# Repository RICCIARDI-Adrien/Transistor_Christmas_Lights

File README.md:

# Transistor Christmas Lights

A really simple blinking Christmas lights using only bipolar transistors for its logic.

## Circuits

The board is made of 2 separate circuits : the motherboard and the light.  
The motherboard circuit holds the logic while the light circuit contains the leds.  
The light circuit should be manufactured in about 20 copies.

## Circuit simulation

The circuit concept is simulated with [Logisim Evolution](https://github.com/logisim-evolution/logisim-evolution) version 3.7.2, the Logisim file is located [here](Motherboard/Simulation/Logisim_Simulation.circ).  
I tried to keep the gates count as low as possible and I tried to select gates that also minimize the transistors count.  
The Logicim file gathers some different tests for the same logic block, all these tests are still present in the file if needed.

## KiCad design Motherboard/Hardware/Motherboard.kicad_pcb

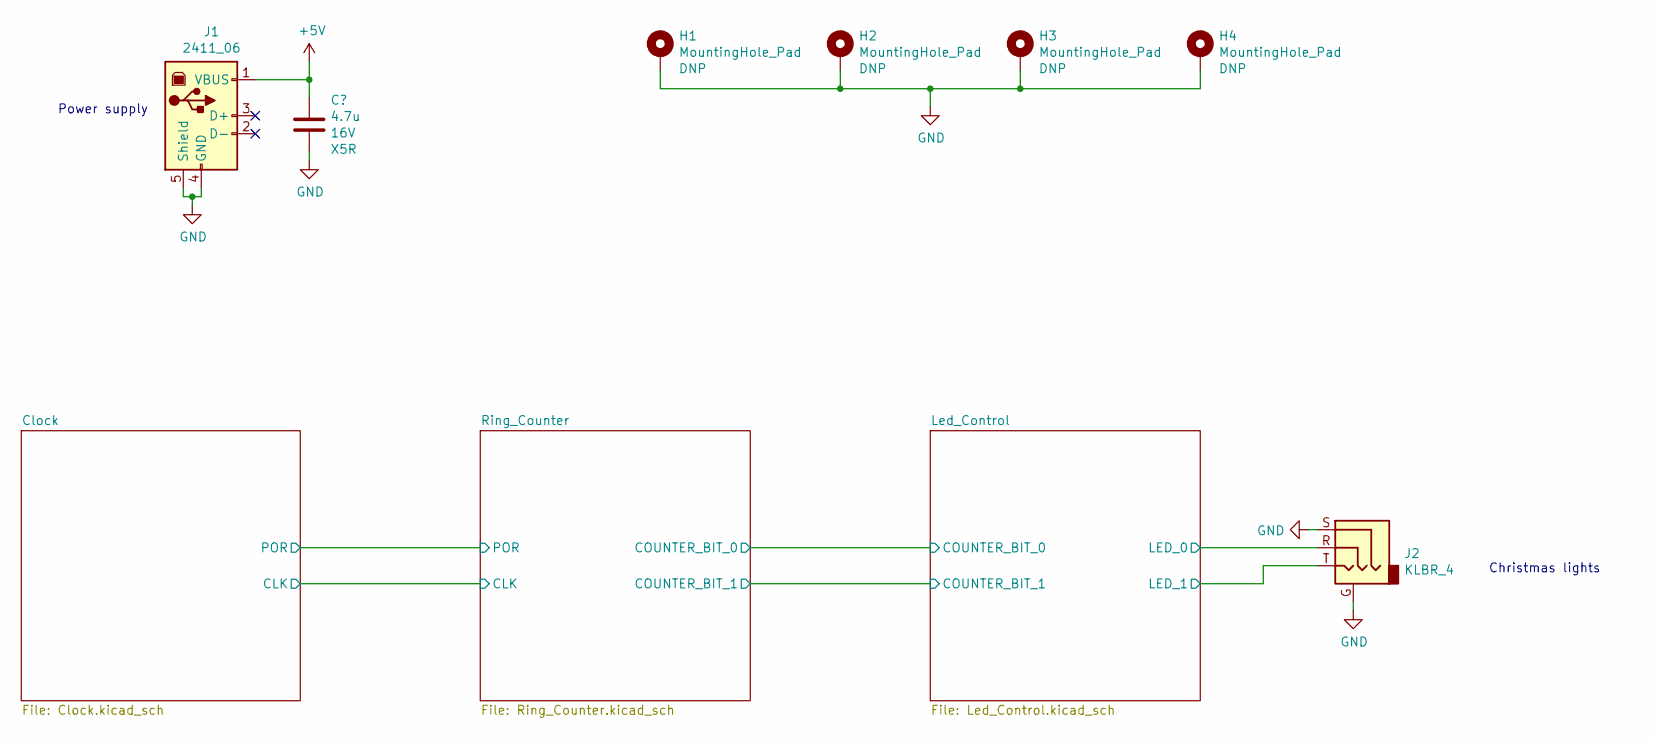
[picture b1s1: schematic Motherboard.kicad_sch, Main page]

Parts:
C1: 4.7u; C_0805_2012Metric_Pad1.18x1.45mm_HandSolder; PartNumber CL21A475KOFNNNE
H1, H2, H3, H4: MountingHole_Pad; MountingHole_4.5mm_Pad
J1: 2411_06; USB_B_OST_USB-B1HSxx_Horizontal; PartNumber 2411_06
J2: KLBR_4; PartNumber KLBR_4

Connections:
/Led_Control/LED_0: J2.R; also elsewhere on the board
/Led_Control/LED_1: J2.T; also elsewhere on the board
GND: C1.2, H1.1, H2.1, H3.1, H4.1, J1.4 (GND), J1.5 (Shield), J2.G, J2.S; also elsewhere on the board

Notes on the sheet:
Power supply
Christmas lights

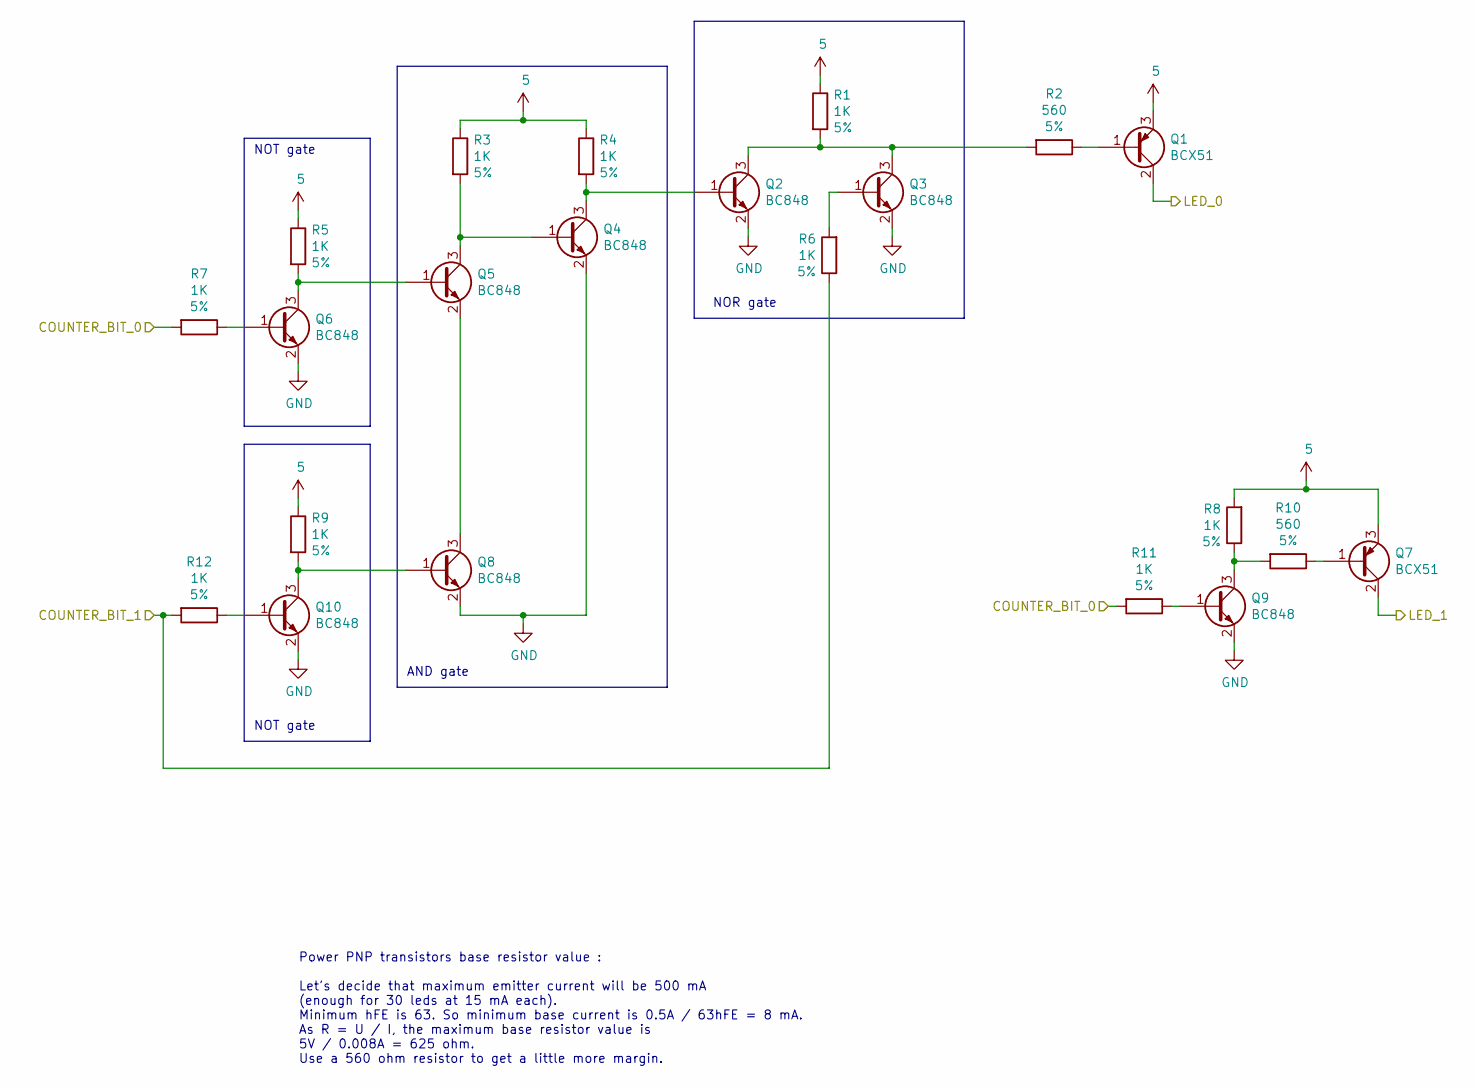
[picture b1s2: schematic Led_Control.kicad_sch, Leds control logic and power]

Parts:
Q1, Q7: BCX51; SOT-89-3; PartNumber BCX51,115
Q2, Q3, Q4, Q5, Q6, Q8, Q9, Q10: BC848; SOT-23
R1, R3, R4, R5, R6, R7, R8, R9, R11, R12: 1K; R_0603_1608Metric_Pad0.98x0.95mm_HandSolder
R2, R10: 560; R_0603_1608Metric_Pad0.98x0.95mm_HandSolder

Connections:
/Led_Control/COUNTER_BIT_0: R7.2, R11.2; also elsewhere on the board
/Led_Control/COUNTER_BIT_1: R6.1, R12.2; also elsewhere on the board
/Led_Control/LED_0: Q1.2 (C); also elsewhere on the board
/Led_Control/LED_1: Q7.2 (C); also elsewhere on the board
GND: Q2.2 (E), Q3.2 (E), Q4.2 (E), Q6.2 (E), Q8.2 (E), Q9.2 (E), Q10.2 (E); also elsewhere on the board
unnamed: Q1.1 (B), R2.1
unnamed: Q2.1 (B), Q4.3 (C), R4.2
unnamed: Q2.3 (C), Q3.3 (C), R1.2, R2.2
unnamed: Q3.1 (B), R6.2
unnamed: Q4.1 (B), Q5.3 (C), R3.2
unnamed: Q5.1 (B), Q6.3 (C), R5.2
unnamed: Q5.2 (E), Q8.3 (C)
unnamed: Q6.1 (B), R7.1
unnamed: Q7.1 (B), R10.1
unnamed: Q9.1 (B), R11.1
unnamed: Q9.3 (C), R8.1, R10.2
unnamed: Q10.1 (B), R12.1
unnamed: Q8.1 (B), Q10.3 (C), R9.2

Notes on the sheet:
NOT gate
Power PNP transistors base resistor value : Let's decide that maximum emitter current will be 500 mA (enough for 30 leds at 15 mA each). Minimum hFE is 63. So minimum base current is 0.5A / 63hFE = 8 mA. As R = U / I, the maximum base resistor value is 5V / 0.008A = 625 ohm. Use a 560 ohm resistor 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
NOR gate
AND gate

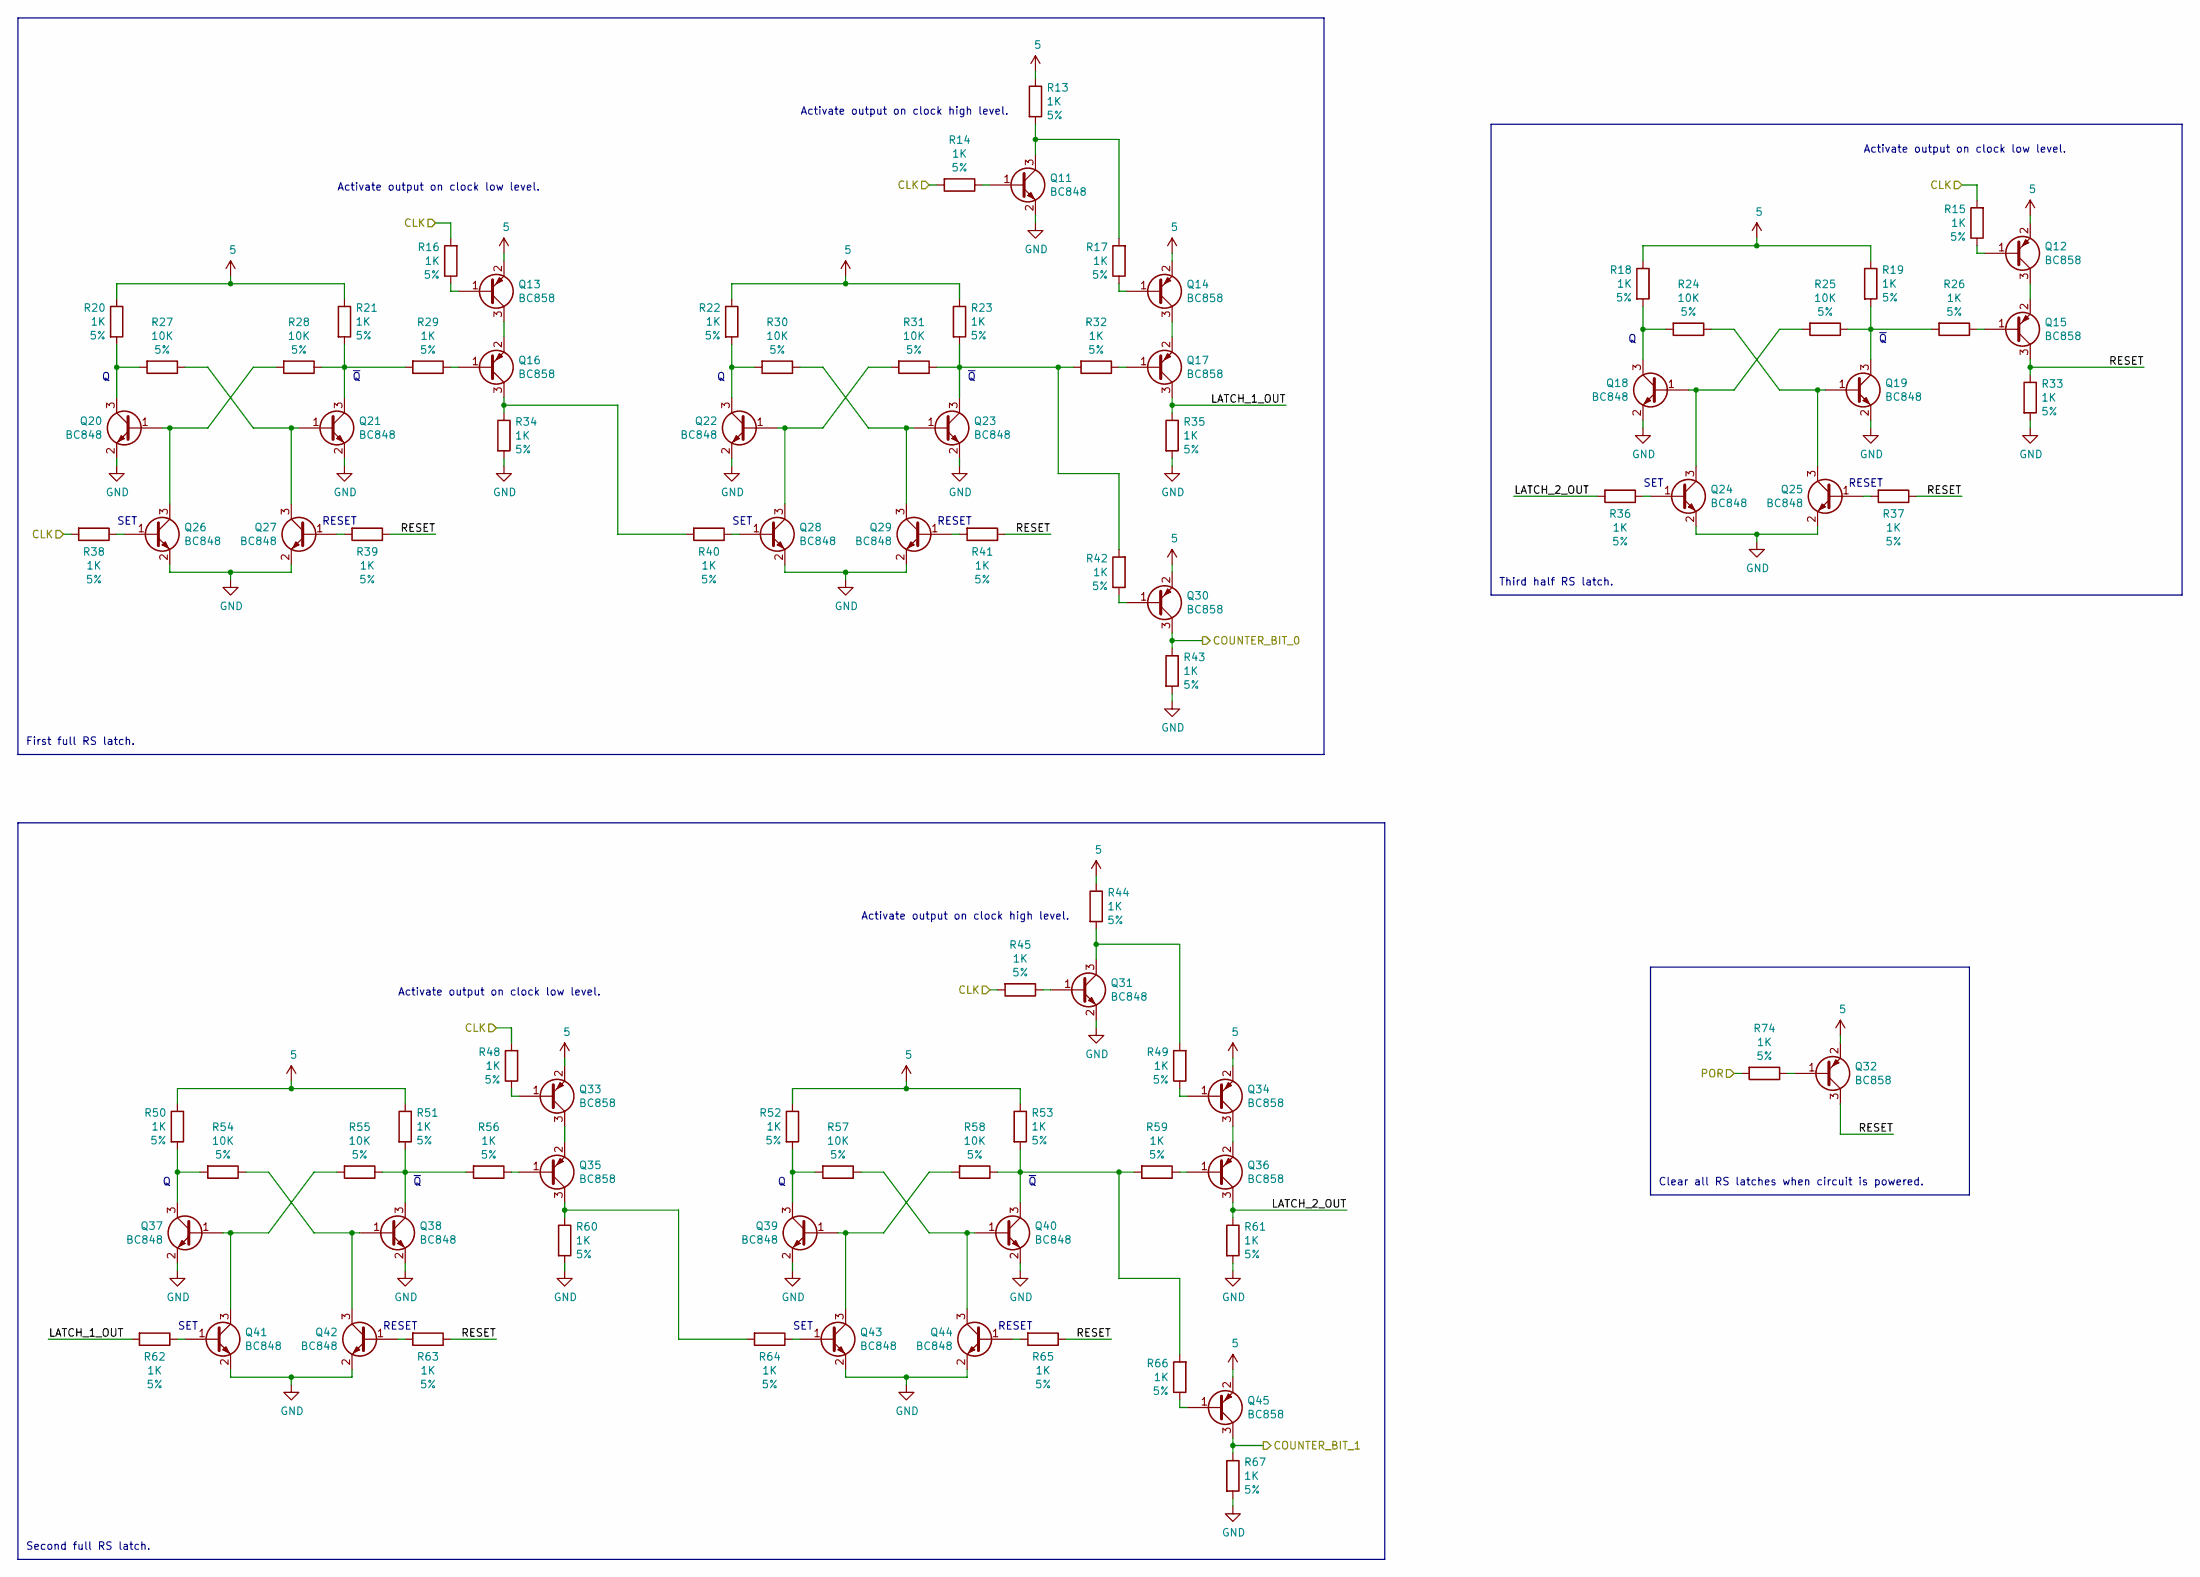
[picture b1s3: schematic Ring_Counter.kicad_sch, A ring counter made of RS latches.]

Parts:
Q11, Q18, Q19, Q20, Q21, Q22, Q23, Q24, Q25, Q26, Q27, Q28, Q29, Q31, Q37, Q38, Q39, Q40, Q41, Q42, Q43, Q44: BC848; SOT-23
Q12, Q13, Q14, Q15, Q16, Q17, Q30, Q32, Q33, Q34, Q35, Q36, Q45: BC858; SOT-23
R13, R14, R15, R16, R17, R18, R19, R20, R21, R22, R23, R26, R29, R32, R33, R34, R35, R36, R37, R38, R39, R40, R41, R42, R43, R44, R45, R48, R49, R50, R51, R52, R53, R56, R59, R60, R61, R62, R63, R64, R65, R66, R67, R74: 1K; R_0603_1608Metric_Pad0.98x0.95mm_HandSolder
R24, R25, R27, R28, R30, R31, R54, R55, R57, R58: 10K; R_0603_1608Metric_Pad0.98x0.95mm_HandSolder

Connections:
/Clock/CLK: R14.2, R15.2, R16.2, R38.2, R45.2, R48.2; also elsewhere on the board
/Clock/POR: R74.2; also elsewhere on the board
/Led_Control/COUNTER_BIT_0: Q30.3 (C), R43.1; also elsewhere on the board
/Led_Control/COUNTER_BIT_1: Q45.3 (C), R67.1; also elsewhere on the board
/Ring_Counter/LATCH_1_OUT: Q17.3 (C), R35.1, R62.2
/Ring_Counter/LATCH_2_OUT: Q36.3 (C), R36.2, R61.1
/Ring_Counter/RESET: Q15.3 (C), Q32.3 (C), R33.1, R37.1, R39.1, R41.1, R63.1, R65.1
GND: Q11.2 (E), Q18.2 (E), Q19.2 (E), Q20.2 (E), Q21.2 (E), Q22.2 (E), Q23.2 (E), Q24.2 (E), Q25.2 (E), Q26.2 (E), Q27.2 (E), Q28.2 (E), Q29.2 (E), Q31.2 (E), Q37.2 (E), Q38.2 (E), Q39.2 (E), Q40.2 (E), Q41.2 (E), Q42.2 (E), Q43.2 (E), Q44.2 (E), R33.2, R34.2, R35.2, R43.2, R60.2, R61.2, R67.2; also elsewhere on the board
unnamed: Q11.1 (B), R14.1
unnamed: Q11.3 (C), R13.2, R17.2
unnamed: Q12.1 (B), R15.1
unnamed: Q12.3 (C), Q15.2 (E)
unnamed: Q13.1 (B), R16.1
unnamed: Q13.3 (C), Q16.2 (E)
unnamed: Q14.1 (B), R17.1
unnamed: Q14.3 (C), Q17.2 (E)
unnamed: Q15.1 (B), R26.1
unnamed: Q16.1 (B), R29.1
unnamed: Q16.3 (C), R34.1, R40.2
unnamed: Q17.1 (B), R32.1
unnamed: Q18.1 (B), Q24.3 (C), R25.2
unnamed: Q18.3 (C), R18.2, R24.2
unnamed: Q19.1 (B), Q25.3 (C), R24.1
unnamed: Q19.3 (C), R19.2, R25.1, R26.2
unnamed: Q20.1 (B), Q26.3 (C), R28.2
unnamed: Q20.3 (C), R20.2, R27.2
unnamed: Q21.1 (B), Q27.3 (C), R27.1
unnamed: Q21.3 (C), R21.2, R28.1, R29.2
unnamed: Q22.1 (B), Q28.3 (C), R31.2
unnamed: Q22.3 (C), R22.2, R30.2
unnamed: Q23.1 (B), Q29.3 (C), R30.1
unnamed: Q23.3 (C), R23.2, R31.1, R32.2, R42.2
unnamed: Q24.1 (B), R36.1
unnamed: Q25.1 (B), R37.2
unnamed: Q26.1 (B), R38.1
unnamed: Q27.1 (B), R39.2
unnamed: Q28.1 (B), R40.1
unnamed: Q29.1 (B), R41.2
unnamed: Q30.1 (B), R42.1
unnamed: Q31.1 (B), R45.1
unnamed: Q31.3 (C), R44.2, R49.2
unnamed: Q32.1 (B), R74.1
unnamed: Q33.1 (B), R48.1
unnamed: Q33.3 (C), Q35.2 (E)
unnamed: Q34.1 (B), R49.1
unnamed: Q34.3 (C), Q36.2 (E)
unnamed: Q35.1 (B), R56.1
unnamed: Q35.3 (C), R60.1, R64.2
unnamed: Q36.1 (B), R59.1
unnamed: Q37.1 (B), Q41.3 (C), R55.2
unnamed: Q37.3 (C), R50.2, R54.2
unnamed: Q38.1 (B), Q42.3 (C), R54.1
unnamed: Q38.3 (C), R51.2, R55.1, R56.2
unnamed: Q39.1 (B), Q43.3 (C), R58.2
unnamed: Q39.3 (C), R52.2, R57.2
unnamed: Q40.1 (B), Q44.3 (C), R57.1
unnamed: Q40.3 (C), R53.2, R58.1, R59.2, R66.2
unnamed: Q41.1 (B), R62.1
unnamed: Q42.1 (B), R63.2
unnamed: Q43.1 (B), R64.1
unnamed: Q44.1 (B), R65.2
unnamed: Q45.1 (B), R66.1

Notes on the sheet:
Third half RS latch.
SET
~{Q}
RESET
Clear all RS latches when circuit is powered.
Activate output on clock low level.
First full RS latch.
Activate output on clock high level.
Second full RS latch.

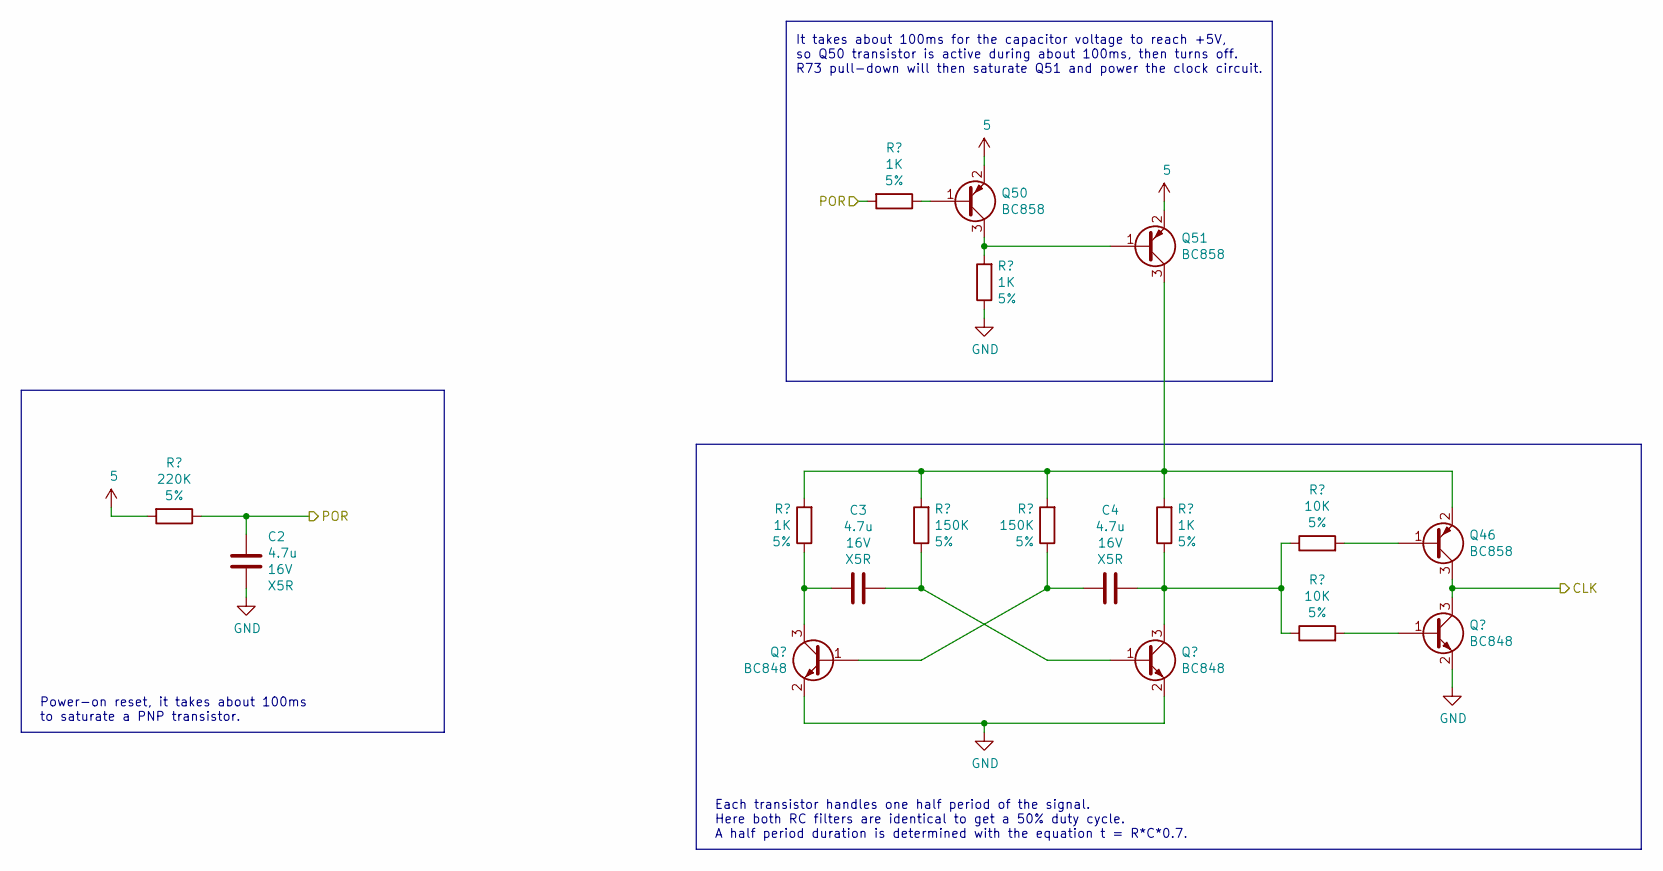
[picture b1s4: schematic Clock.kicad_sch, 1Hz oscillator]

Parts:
C2, C3, C4: 4.7u; C_0805_2012Metric_Pad1.18x1.45mm_HandSolder; PartNumber CL21A475KOFNNNE
Q46, Q50, Q51: BC858; SOT-23
Q47, Q48, Q49: BC848; SOT-23
R46: 220K; R_0603_1608Metric_Pad0.98x0.95mm_HandSolder
R47, R68, R71, R73: 1K; R_0603_1608Metric_Pad0.98x0.95mm_HandSolder
R69, R70: 150K; R_0603_1608Metric_Pad0.98x0.95mm_HandSolder
R72, R75: 10K; R_0603_1608Metric_Pad0.98x0.95mm_HandSolder

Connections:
/Clock/CLK: Q46.3 (C), Q47.3 (C); also elsewhere on the board
/Clock/POR: C2.1, R46.1, R47.2; also elsewhere on the board
GND: C2.2, Q47.2 (E), Q48.2 (E), Q49.2 (E), R73.1; also elsewhere on the board
unnamed: Q46.1 (B), R72.2
unnamed: Q46.2 (E), Q51.3 (C), R68.2, R69.2, R70.2, R71.2
unnamed: Q47.1 (B), R75.2
unnamed: C4.2, Q48.1 (B), R70.1
unnamed: C3.2, Q48.3 (C), R68.1
unnamed: C3.1, Q49.1 (B), R69.1
unnamed: C4.1, Q49.3 (C), R71.1, R72.1, R75.1
unnamed: Q50.1 (B), R47.1
unnamed: Q50.3 (C), Q51.1 (B), R73.2

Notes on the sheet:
It takes about 100ms for the capacitor voltage to reach +5V, so Q50 transistor is active during about 100ms, then turns off. R73 pull-down will then saturate Q51 and power the clock circuit.
Each transistor handles one half period of the signal. Here both RC filters are identical to get a 50% duty cycle. A half period duration is determined with the equation t = R*C*0.7.
Power-on reset, it takes about 100ms to saturate a PNP transistor.

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
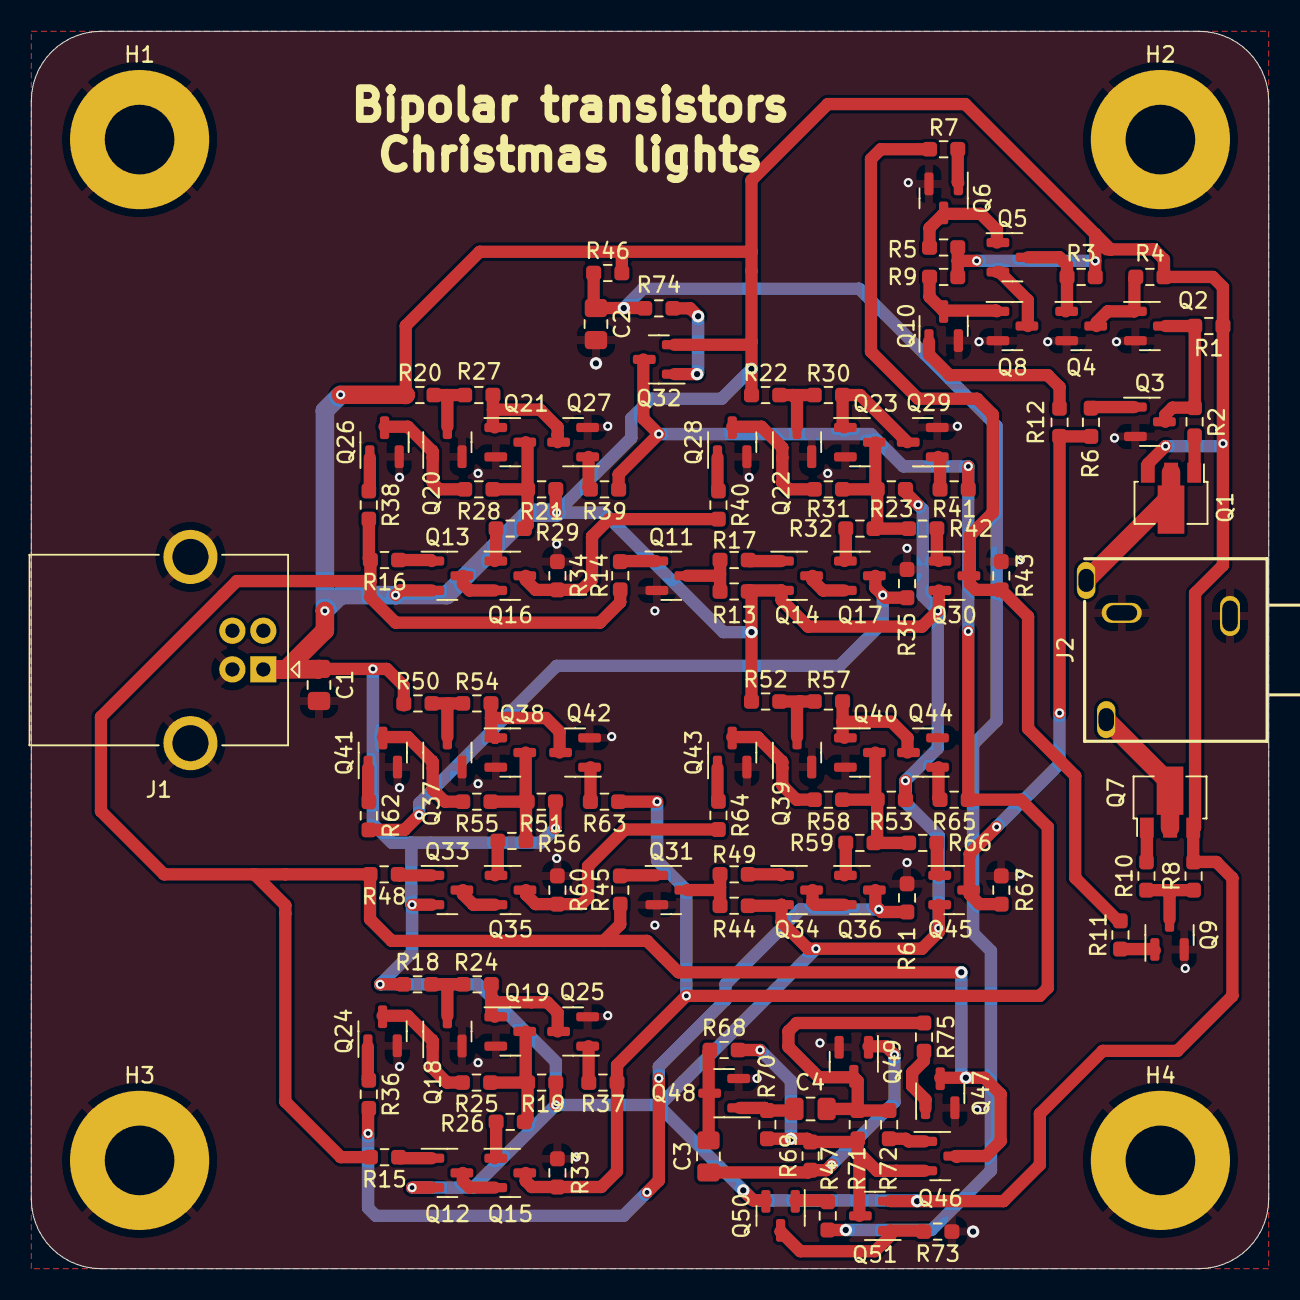
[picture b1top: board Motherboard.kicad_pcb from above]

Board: 2 copper layers, 80.0 x 80.0 mm, 136 parts (0 on the bottom side), 87 nets.

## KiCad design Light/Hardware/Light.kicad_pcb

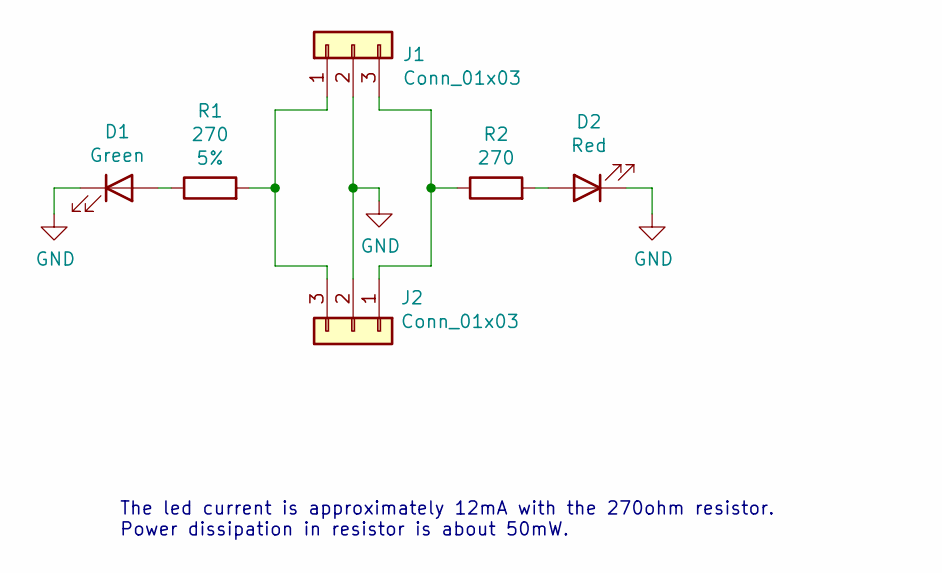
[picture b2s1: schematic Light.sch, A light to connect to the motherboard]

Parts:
D1: Green; LED_D5.0mm_Horizontal_O1.27mm_Z3.0mm
D2: Red; LED_D5.0mm_Horizontal_O1.27mm_Z3.0mm
J1, J2: Conn_01x03; PinHeader_1x03_P2.54mm_Horizontal
R1, R2: 270; R_1206_3216Metric_Pad1.30x1.75mm_HandSolder

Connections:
GND: D1.1 (K), D2.1 (K), J1.2, J2.2
unnamed: D1.2 (A), R1.1
unnamed: D2.2 (A), R2.2
unnamed: J1.1, J2.3, R1.2
unnamed: J1.3, J2.1, R2.1

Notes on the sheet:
The led current is approximately 12mA with the 270ohm resistor. Power dissipation in resistor is about 50mW.

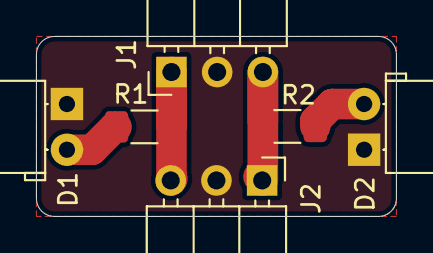
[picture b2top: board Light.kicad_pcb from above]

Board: 2 copper layers, 20.0 x 10.0 mm, 6 parts (0 on the bottom side), 5 nets.

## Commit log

2021-12-29 Added a circuit concept simulation based on logic gates.
2021-12-29 Added MIT license.
2021-12-30 Created the PCB KiCad project. Added a test circuit to setup the circuit SPICE simulation.
2022-01-01 Added led control logic to schematic. The second led power transistor will be added later.
2022-01-04 Added a ring counter circuit made only of RS latches to the Logicim simulation.
2022-01-04 Removed an unused RS latch in the Logisim ring counter circuit.
2022-01-04 Added the ring counter to the schematic.
2022-01-20 Improved ring counter RS latches output with better signal quality and less transistors count.
2022-01-20 Added second led logic and power transistor, also added BC858 SPICE model.
2022-02-16 Added RS latches power-on reset.
2022-02-16 Added oscillator to schematic.
2022-02-16 Moved motherboard hardware design to a dedicated directory to make room for the christmas lights board.
2022-02-16 Added light board schematic.
2022-02-17 Added light board PCB.
2022-02-17 Renamed motherboard KiCad project for more coherency.
2022-02-17 Added power supply and Christmas lights connectors to motherboard schematic.
2022-02-17 Renamed all motherboard components so the name are ordered.
2022-02-21 Placed most of the components on the PCB.
2022-02-21 Adapted KLBR 4 jack socket footprint pins naming to match KiCad default symbol.
2022-02-21 Placed all components and mounting holes on PCB.
2022-02-21 Routed PCB.
2022-02-23 Disabled the motherboard clock circuit power supply while power-on reset delay is running to avoid clocking the RS gates while they are being reset by the power-on reset.
2022-02-23 Added more component details to the 'light' schematic.
2022-02-23 Added more information about the two circuits to the README.md.
2022-03-16 Fixed clock output push-pull stage in schematic.
2023-11-15 Updated the motherboard schematic to KiCad 7.
2023-11-15 Updated the motherboard PCB to KiCad 7.
2023-11-15 Added the missing courtyard information to the KLBR 4 jack connector footprint and updated the motherboard PCB accordingly.
2023-11-15 Added round corners to the motherboard PCB.
2023-11-15 Excluded the motherboard connectors and the mounting holes from the simulation.
